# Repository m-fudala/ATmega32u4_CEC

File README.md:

# ATmega32U4 CEC device
## Software
HDMI CEC protocol has been programmed using GPIO pins and timers.\
Full protocol feature set is to be done (address setting, commands etc.).&nbsp;&nbsp;

Sample message sent and received:

## Hardware
PCB has been designed as a pass-through between media player and a TV. Arduino Pro Micro is used as the brains of the device.
\

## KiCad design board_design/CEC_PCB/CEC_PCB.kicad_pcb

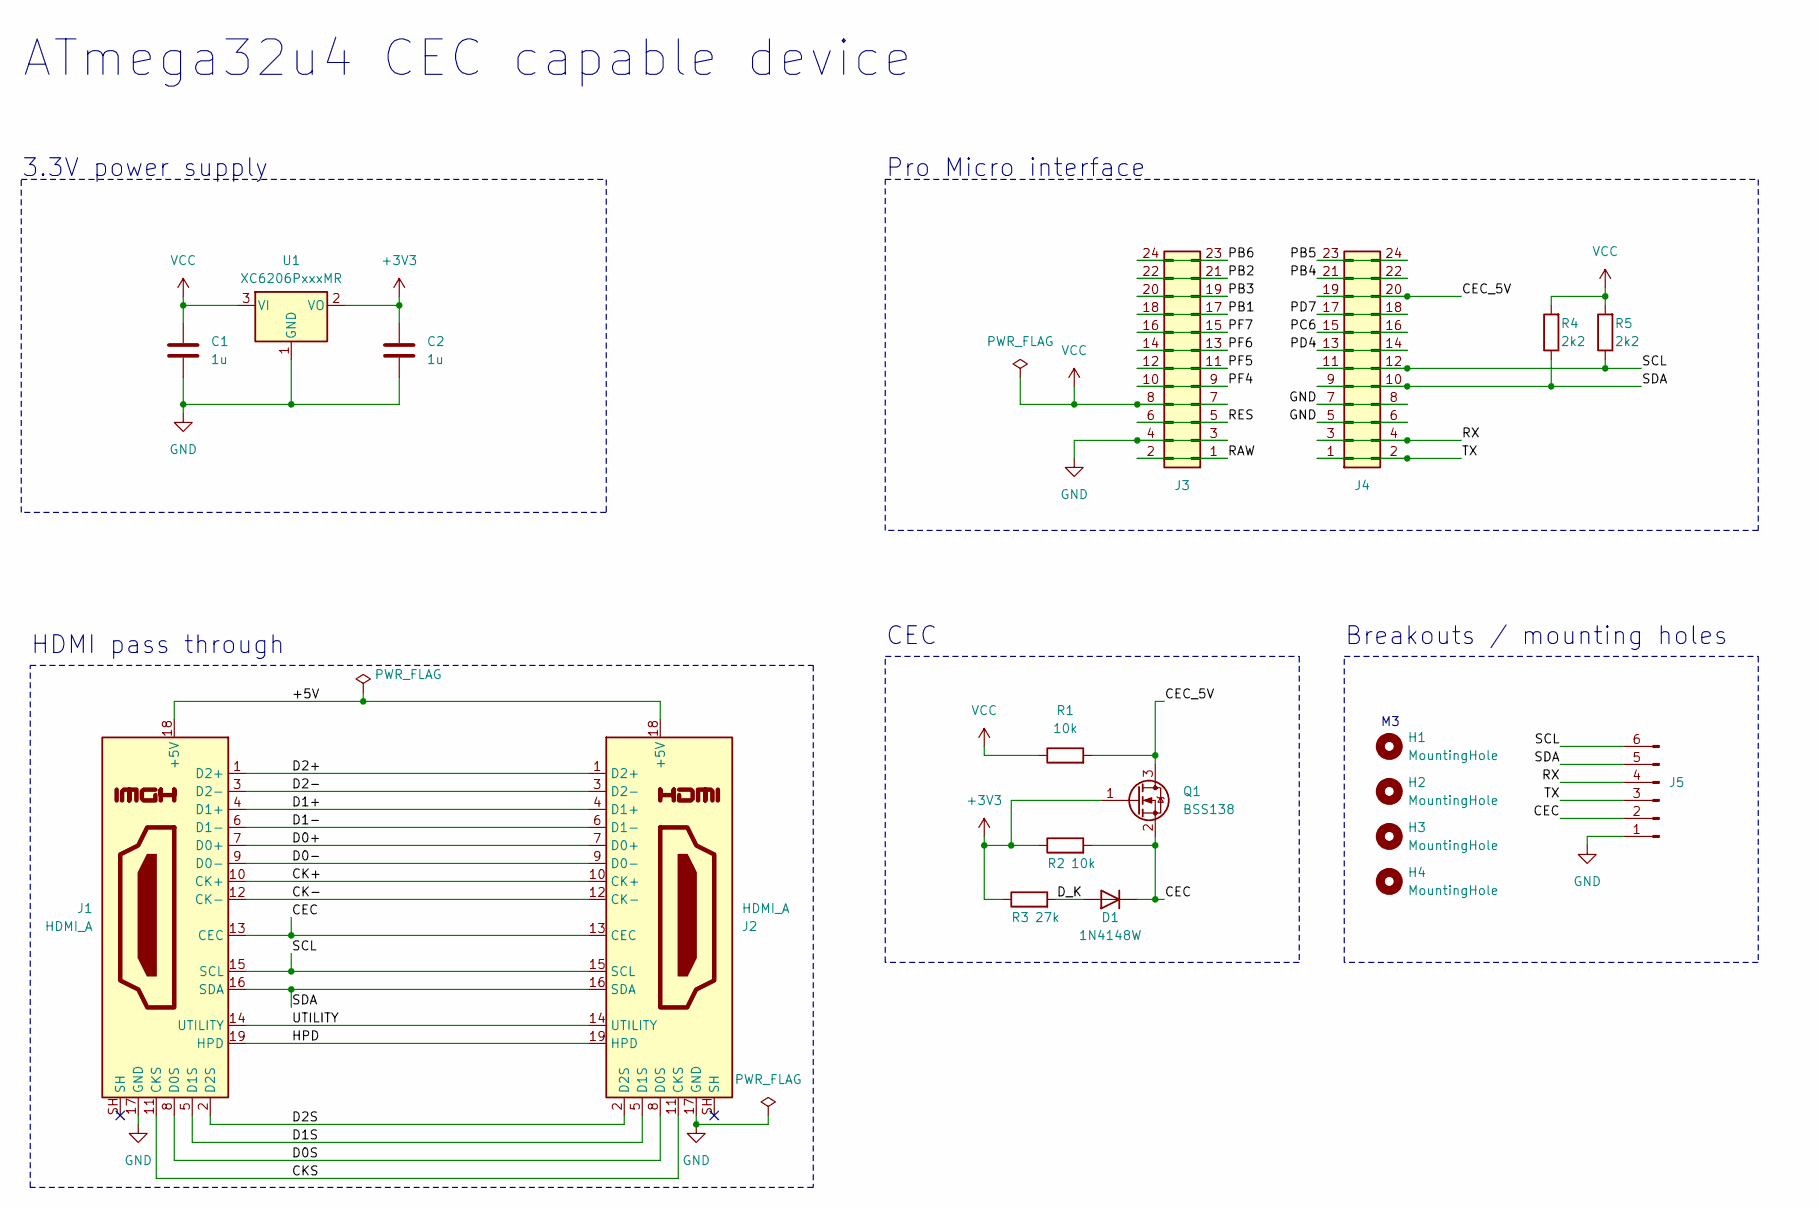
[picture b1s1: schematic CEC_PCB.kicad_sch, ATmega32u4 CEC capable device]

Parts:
C1, C2: 1u; C_0402_1005Metric
D1: 1N4148W; D_SOD-123
H1, H2, H3, H4: MountingHole; MountingHole_3mm
J1, J2: HDMI_A; HDMI_A_Contact_Technology_HDMI-19APL2_Horizontal
J3, J4: Conn_02x12_Odd_Even; PinSocket_2x12_P2.54mm_Vertical
J5: Conn_01x06_Pin; PinHeader_1x06_P2.54mm_Vertical
Q1: BSS138; SOT-23
R1, R2: 10k; R_0402_1005Metric
R3: 27k; R_0402_1005Metric
R4, R5: 2k2; R_0402_1005Metric
U1: XC6206PxxxMR; SOT-23-3

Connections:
+3V3: C2.1, Q1.1 (G), R2.1, R3.1, U1.2 (VO)
/+5V: J1.18 (+5V), J2.18 (+5V)
/CEC: D1.1 (K), J1.13 (CEC), J2.13 (CEC), J5.2, Q1.2 (S), R2.2
/CEC_5V: J3.19, J3.20, Q1.3 (D), R1.2
/CK+: J1.10 (CK+), J2.10 (CK+)
/CK-: J1.12 (CK-), J2.12 (CK-)
/CKS: J1.11 (CKS), J2.11 (CKS)
/D0+: J1.7 (D0+), J2.7 (D0+)
/D0-: J1.9 (D0-), J2.9 (D0-)
/D0S: J1.8 (D0S), J2.8 (D0S)
/D1+: J1.4 (D1+), J2.4 (D1+)
/D1-: J1.6 (D1-), J2.6 (D1-)
/D1S: J1.5 (D1S), J2.5 (D1S)
/D2+: J1.1 (D2+), J2.1 (D2+)
/D2-: J1.3 (D2-), J2.3 (D2-)
/D2S: J1.2 (D2S), J2.2 (D2S)
/D_K: D1.2 (A), R3.2
/HPD: J1.19 (HPD), J2.19 (HPD)
/PB1: J4.17, J4.18
/PB2: J4.21, J4.22
/PB3: J4.19, J4.20
/PB4: J3.21, J3.22
/PB5: J3.23, J3.24
/PB6: J4.23, J4.24
/PC6: J3.15, J3.16
/PD4: J3.13, J3.14
/PD7: J3.17, J3.18
/PF4: J4.9, J4.10
/PF5: J4.11, J4.12
/PF6: J4.13, J4.14
/PF7: J4.15, J4.16
/RAW: J4.1, J4.2
/RES: J4.5, J4.6
/RX: J3.3, J3.4, J5.4
/SCL: J1.15 (SCL), J2.15 (SCL), J3.11, J3.12, J5.6, R5.1
/SDA: J1.16 (SDA), J2.16 (SDA), J3.9, J3.10, J5.5, R4.1
/TX: J3.1, J3.2, J5.3
/UTILITY: J1.14 (UTILITY), J2.14 (UTILITY)
GND: C1.2, C2.2, J1.17 (GND), J2.17 (GND), J3.5, J3.6, J3.7, J3.8, J4.3, J4.4, J5.1, U1.1 (GND)
VCC: C1.1, J4.7, J4.8, R1.1, R4.2, R5.2, U1.3 (VI)

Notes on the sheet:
Breakouts / mounting holes
CEC
HDMI pass through
Pro Micro interface
ATmega32u4 CEC capable device
3.3V power supply

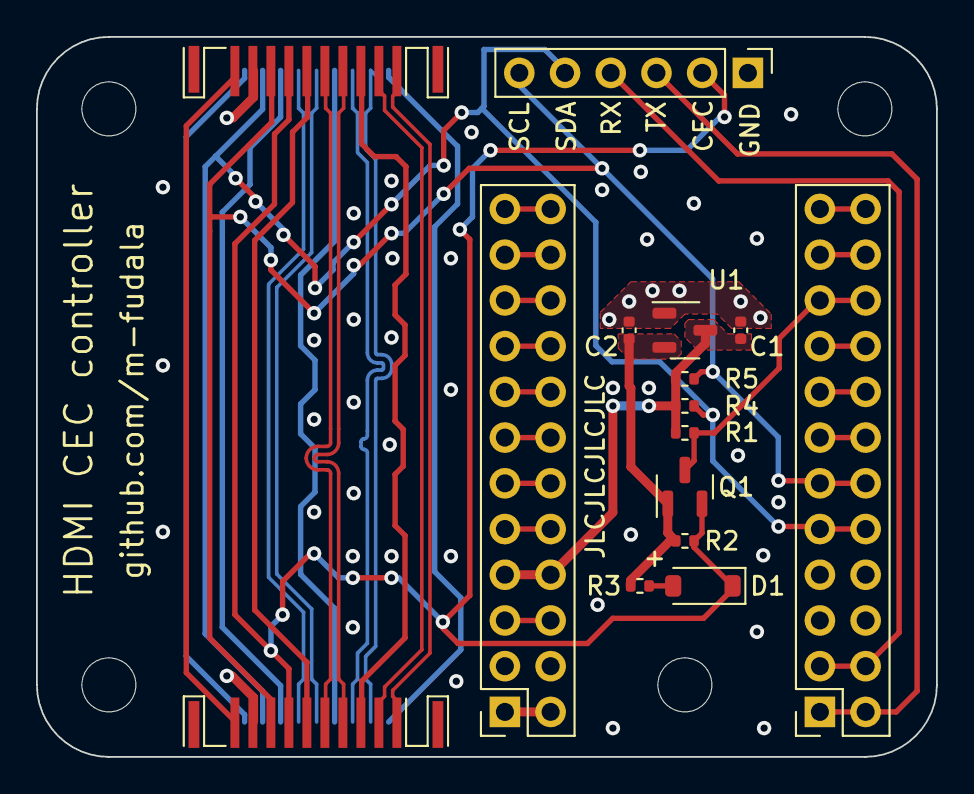
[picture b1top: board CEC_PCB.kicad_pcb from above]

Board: 4 copper layers, 50.0 x 40.0 mm, 19 parts (0 on the bottom side), 40 nets.

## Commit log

2024-02-20 Libraries added
2024-02-20 File prototypes
2024-02-20 Serial communication based on commands
2024-02-23 Basic initialization and sending start bit
2024-02-23 Library update pulled
2024-02-27 Sending start bit
2024-02-29 Sending a byte
2024-02-29 Button used for debugging purposes
2024-03-01 Bus status as bit field Interrupt 6 added to bus Option to set device as initiator or follower
2024-03-01 Sending multiple bytes Function for inserting EOM
2024-03-01 Prototype of receiver
2024-03-01 Sending received bytes on serial
2024-03-01 Waiting for ACK
2024-03-01 Transmitting without waiting
2024-03-04 Small fix
2024-03-04 Transmission working fully hopefully
2024-03-04 Debugs on receiving
2024-03-05 Small RX fix
2024-03-06 Fix for bits not being saved
2024-03-06 Only setting timer interrupts when needed TX and IO debugs Waiting for ACK on TX side Prototype of sending ACK on RX
2024-03-07 Bus is properly released instead of going high
2024-03-07 Fixed RX and some upkeeping
2024-03-11 Messages can be transmitted and received more than once
2024-03-13 Perfboard design
2024-03-14 Pro Micro pins are broken out
2024-03-15 Fixed some design issues
2024-03-19 Fix for follower not being established after sending Fixed some issues in board's design
2024-03-19 Prototype PCB design files .gitignore updated with KiCad backup files
2024-03-19 HDMI connectors Board stackup and constraints Pre-defiened sizes Schematic prototype
2024-03-19 LDO for 3.3V power CEC level shifting I2C pull-up resistors
2024-03-19 Broke out Pro Micro pins using a connector with two rows Level shifter between CEC pins Mounting holes and debug pins PCB outline defined Crude component placement Copper pours on GND planes
2024-03-20 Labels for nets in the schematic Board size change Parts placement change Basic routing
2024-03-20 Track routing done
2024-03-21 Optimizations and silkscreen annotations
2024-03-21 Changed VDO capacitors to 1uF Some routing changes Ground vias throughout the PCB Some optimizations
2024-03-28 Final PCB touches
2024-04-05 Reacting only to address 0x4 Small fixes
2024-04-10 Reacting to specific address and broadcasts Debugs are disabled
2024-04-10 Prototype of responding to messages
2024-04-15 File containing CEC opcodes and data unions
2024-04-15 Reacting to opcodes from cec_commands.h Sending only directly addressed messages to UART Sending Active Source from UART command TX workaround: waiting for ACK only when directly addressing
2024-04-15 Fixed sending every time a message is received Responding to Give OSD Name command
2024-04-19 New commands for sending Standby, Image View On Some upkeeping
2024-04-22 Sending received bytes as characters on UART Use of defines Fixed TX bug when sending for the first time
2024-04-24 Usage of Timer 3 to count bus idle time Waiting automatically for 5 bit times of idle bus
2024-04-24 Setting address automatically based on variable in hdmi_cec.c Volume up and volume down commands (without releasing afterwards)
2024-04-30 Sending debug on TX New commands: Mute and Set OSD String
2024-04-30 Fixed Device Vendor ID command New commands Sending Feature Abort when opcode is not recognized
2024-04-30 Sending Deck Status Reacting to Vendor Commands
2024-12-15 Added description
